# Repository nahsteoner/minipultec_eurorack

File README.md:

# OnerLAB BoCu

Module Eurorack **stéréo de fin de chaîne** : EQ type Pultec (sans tubes) + saturation douce à diodes + sorties jack 6,35 mm balanced.

- **Format** : 16 HP, 3U, alimentation ±12 V (header Doepfer 10 broches)
- **Entrées** : 2 × jack 3,5 mm mono (standard Eurorack), normalisées L → R
- **Sorties** : 2 × jack 6,35 mm TRS balanced (L / R)
- **PCB** : KiCad 7, netlist complète, **non routé** (placement fin + autorouter à ta main)
- **Fab** : pensé JLCPCB / LCSC, SMD 0603/0805 + SOIC-8

## Face avant

```
        OnerLAB BoCu
   [ LOW BOOST ]   [ LOW CUT ]
        [FREQ L] [FREQ R]     40 / 80 / 120 Hz
   [ MID CUT   ]   [ HIGH BOOST ]
   (LED sat L)         (LED sat R)
   IN L   IN R      OUT L   OUT R     ← jacks en bas
```

Les 4 pots sont **double piste** (L+R ensemble). Les deux rotatifs de fréquence sont **indépendants** (L et R).

## Le circuit, en une phrase

Buffer d'entrée → pad passif + mid-cut à gyrator → low-cut RC → makeup NE5532 avec **boost grave RLC (gyrator 11 H)** et **shelf aigu**, diodes Si/LED asymétriques dans la contre-réaction, puis driver balanced (hot + inverseur).

C'est un Pultec « inventé » en solide :

| Contrôle | Comportement simulé |
|---|---|
| Low boost | cloche ~+10 dB à 40 / 80 / 120 Hz, Q ≈ 1 |
| Low cut | shelf grave ~−11 dB, coin un peu au-dessus de f₀ |
| **Les deux** | le **Pultec trick** : bosse sur f₀ + creux de mud juste au-dessus |
| Mid cut | cloche ~−9 dB vers 500 Hz |
| High boost | shelf +8 à +10 dB vers 8–16 kHz |
| Diodes | propre à bas niveau (THD 0,08 % @ 0,5 V), couleur paire type lampe dès ~1,5 V |

Courbes : [`docs/curves/`](docs/curves/)

Relancer les sims : `python3 sim/simulate_bocu.py`

## Fichiers KiCad

| Fichier | Rôle |
|---|---|
| `hardware/OnerLAB_BoCu.kicad_pcb` | PCB 78 × 118 mm, 120 footprints, **94 nets**, ratsnest prêt |
| `hardware/OnerLAB_BoCu.net` | Netlist KiCad (source de vérité électrique) |
| `hardware/OnerLAB_BoCu_panel.kicad_pcb` | Face avant 16 HP, trous uniquement |
| `hardware/BOM_LCSC.csv` | BOM + codes LCSC (SMT) |
| `hardware/libraries/` | Switch 2P3T custom |

Pas de schéma dessiné : tout part de `tools/generate_kicad.py` (SKiDL). Tu n'en as pas besoin pour router.

### Chez toi dans KiCad 7

1. Ouvre `hardware/OnerLAB_BoCu.kicad_pcb`.
2. **Place** les SMD (ils sont en grille volontairement, les jacks/pots/switchs sont déjà en zone façade).
3. Ajoute un plan de masse GND (F.Cu et/ou B.Cu).
4. Autoroute : *Route → Automatically Route Selected* / FreeRouting, ou route à la main les alimentations d'abord.
5. DRC, puis Gerber JLCPCB (2 couches, 1,6 mm, HASL ou ENIG).

Régénérer netlist + PCB vierge :

```bash
python3 tools/generate_kicad.py
python3 tools/place_pcb.py
python3 tools/make_panel.py
```

## JLCPCB / LCSC

- **SMT assemblé** : NE5532DR (`C7426`, Basic), passifs 0603/0805, BAT54S, 1N4148W SOD-123, SS14, ferrites 0805.
- **THT à souder toi-même** (pas Basic JLCPCB) :
  - 2 × Thonkiconn **PJ398SM** (entrées 3,5)
  - 2 × **Neutrik NJ3FD-V** (sorties 6,35 TRS verticales) — un jack LCSC 6,35 vertical TRS peut remplacer, **adapte le footprint**
  - 4 × Alpha **RD902** B50K dual 9 mm
  - 2 × rotatif **SR16 2P3T 16 mm** — le footprint `OnerLAB:SW_Rotary_2P3T_SR16` est un **2×4 au pas 2,54 mm** (A1 A2 A3 A / B1 B2 B3 B). **Vérifie le pinout de TON switch** avant de router, ou déplace les pads.
  - header shrouded 2×5, stripe **rouge = pin 1 = −12 V**
  - 3 × LED 3 mm (pwr + sat L/R)

Les condensateurs qui fixent 40/80/120 Hz et le gyrator 10 nF sont en 0805. Pour un son plus « studio », tu peux remplacer les C de fréquence (1 µF+470 nF, 390 nF, 150 nF, 82/39/27 nF) par du **film THT 5 mm** — laisse des pastilles si tu veux.

Codes LCSC : **revérifie le stock / Basic vs Extended** sur [jlcpcb.com/parts](https://jlcpcb.com/parts) avant commande, les C-numbers bougent.

## Alim & niveaux

- ±12 V, ~80–100 mA / rail (5 × NE5532).
- Entrée ~10 Vpp Eurorack, Z = 100 kΩ, protection BAT54S.
- Sortie balanced un peu chaude (niveau Eurorack différentiel). Un interface ligne l'accepte en général ; sinon pad dans la DAW / l'entrée.

## Mapping pots (rheostat)

| Pot | CCW | CW |
|---|---|---|
| LOW BOOST, MID, HIGH | effet min (50 k) | max (≈ 0 Ω) |
| LOW CUT | bypass (0 Ω) | max cut (50 k) |

Pistes : 1-2-3 = canal L, 4-5-6 = canal R (Alpha RD902).

## Licence / nom

OnerLAB BoCu — projet DIY personnel. Pas un clone Pultec : topologie SSD (gyrators + diodes) calquée sur le *trick* boost+cut.

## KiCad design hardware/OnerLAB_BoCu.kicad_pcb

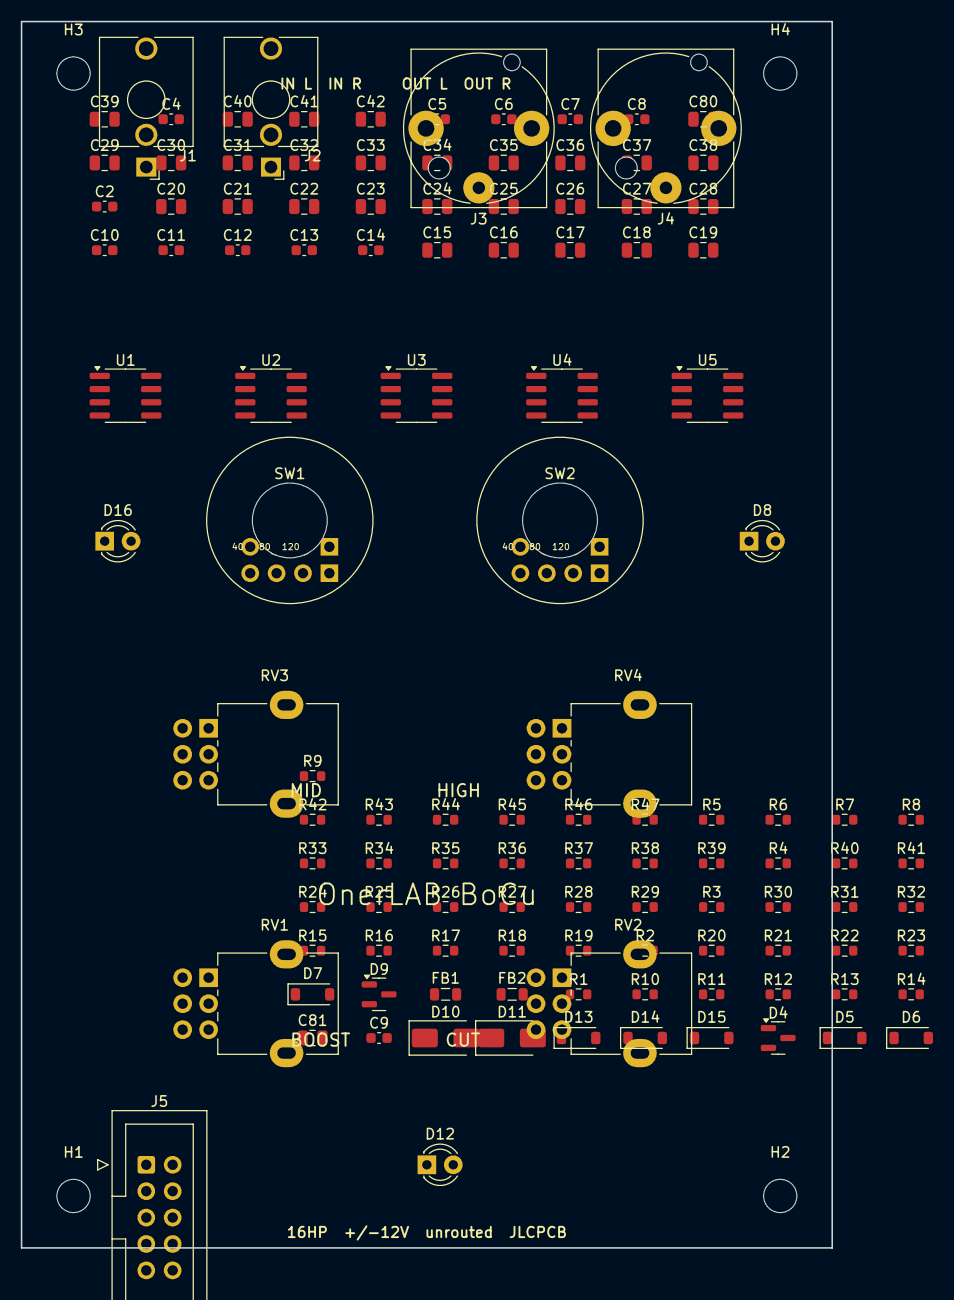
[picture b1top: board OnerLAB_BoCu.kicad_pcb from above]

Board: 2 copper layers, 78.0 x 118.0 mm, 124 parts (0 on the bottom side), 82 nets, no tracks yet.

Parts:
C2, C4, C5, C6, C7, C8, C9, C10, C11, C12, C13, C14: 100n; C_0603_1608Metric
C15, C27, C28, C29, C41, C42, C80, C81: 10u; C_0805_2012Metric
C16, C30: 100n; C_0805_2012Metric
C17, C26, C31, C40: 10n; C_0805_2012Metric
C18, C32: 82n; C_0805_2012Metric
C19, C33: 39n; C_0805_2012Metric
C20, C34: 27n; C_0805_2012Metric
C21, C35: 8.2n; C_0805_2012Metric
C22, C36: 1u; C_0805_2012Metric
C23, C37: 470n; C_0805_2012Metric
C24, C38: 390n; C_0805_2012Metric
C25, C39: 150n; C_0805_2012Metric
D4, D9: BAT54S; SOT-23
D5, D6, D7, D13, D14, D15: 1N4148W; D_SOD-123
D8, D16: LED_SAT; LED_D3.0mm
D10, D11: SS14; D_SMA
D12: LED_PWR; LED_D3.0mm
FB1, FB2: 600R@100MHz; L_0805_2012Metric
H1, H2, H3, H4: M3; MountingHole_3.2mm_M3
J1: IN_L_3.5; Jack_3.5mm_QingPu_WQP-PJ398SM_Vertical_CircularHoles
J2: IN_R_3.5; Jack_3.5mm_QingPu_WQP-PJ398SM_Vertical_CircularHoles
J3: OUT_L_6.35; Jack_6.35mm_Neutrik_NJ3FD-V_Vertical
J4: OUT_R_6.35; Jack_6.35mm_Neutrik_NJ3FD-V_Vertical
J5: EURORACK_10P; IDC-Header_2x05_P2.54mm_Vertical
R1, R7, R8, R9, R12, R19, R20, R30, R31, R32, R35, R42, R43: 10k; R_0603_1608Metric
R2, R22, R24, R25, R45, R47: 100k; R_0603_1608Metric
R3, R6, R26, R29: 1k; R_0603_1608Metric
R4, R5, R27, R28: 4.7k; R_0603_1608Metric
R10, R33: 15k; R_0603_1608Metric
R11, R15, R34, R38: 2.2k; R_0603_1608Metric
R13, R14, R36, R37: 22k; R_0603_1608Metric
R16, R39: 2.7k; R_0603_1608Metric
R17, R18, R40, R41: 33k; R_0603_1608Metric
R21, R23, R44, R46: 220R; R_0603_1608Metric
RV1: B50K_BOOST; Potentiometer_Alpha_RD902F-40-00D_Dual_Vertical
RV2: B50K_CUT; Potentiometer_Alpha_RD902F-40-00D_Dual_Vertical
RV3: B50K_MID; Potentiometer_Alpha_RD902F-40-00D_Dual_Vertical
RV4: B50K_HIGH; Potentiometer_Alpha_RD902F-40-00D_Dual_Vertical
SW1: FREQ_L; SW_Rotary_2P3T_SR16
SW2: FREQ_R; SW_Rotary_2P3T_SR16
U1, U2, U3, U4, U5: NE5532DR; SOIC-8_3.9x4.9mm_P1.27mm

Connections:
+12V: C2.1, C5.1, C7.1, C9.1, C11.1, C13.1, C80.1, D4.2, D9.2, FB1.2, R1.1, U1.8, U2.8, U3.8, U4.8, U5.8
-12V: C4.1, C6.1, C8.1, C10.1, C12.1, C14.1, C81.1, D4.1, D9.1, FB2.2, U1.4, U2.4, U3.4, U4.4, U5.4
GND: C2.2, C4.2, C5.2, C6.2, C7.2, C8.2, C9.2, C10.2, C11.2, C12.2, C13.2, C14.2, C17.2, C21.2, C26.2, C31.2, C35.2, C40.2, C80.2, C81.2, D12.1, J1.S, J2.S, J3.S, J4.S, J5.2, J5.3, J5.4, J5.5, J5.6, R2.2, R5.2, R9.2, R12.2, R22.2, R24.2, R25.2, R28.2, R32.2, R35.2, R45.2, R47.2, U2.5, U4.5
IN_L: C15.1, J1.T, J2.TN, R2.1
IN_R: C29.1, J2.T, R25.1
L_BLK: D4.3, R3.2, U1.3
L_BUF: R4.1, U1.1, U1.2
L_COLD: R20.2, R23.1, U2.7
L_D3: D7.1, R13.1
L_EQ: R4.2, R5.1, R6.1, RV2.1, SW1.B
L_HI: R15.2, RV4.2
L_INVN: R19.2, R20.1, U2.6
L_LB: R16.2, RV1.2
L_LC: RV1.3, SW1.A
L_LG+: C26.1, R17.2, U1.5
L_LL: C22.2, C23.2, C24.2, C25.2, R17.1, R18.2
L_MIDC: C16.1, RV3.3
L_MIDG+: C17.1, R7.2, U5.3
L_MIDL: C16.2, R7.1, R8.2
L_MIDW: R6.2, RV3.2
L_MK: D5.2, R10.1, R14.2, R19.1, R21.1, U2.1
L_NINV: D8.2, R10.2, R11.1, R13.2, R15.1, R16.1, U2.2
L_POST: C18.2, C19.2, C20.2, R9.1, RV2.2, U2.3
L_TAP: R11.2, R12.1
unnamed: D10.1, FB1.1
unnamed: D11.2, FB2.1
unnamed: D12.2, R1.2
unnamed: C15.2, R3.1
unnamed: R8.1, U5.1, U5.2
unnamed: C18.1, SW1.B1
unnamed: C19.1, SW1.B2
unnamed: C20.1, SW1.B3
unnamed: D5.1, D6.2
unnamed: D6.1, D7.2
unnamed: D8.1, R14.1
unnamed: C21.1, RV4.3
unnamed: C22.1, C23.1, SW1.A1
unnamed: C24.1, SW1.A2
unnamed: C25.1, SW1.A3
unnamed: R18.1, U1.6, U1.7
unnamed: C27.2, J3.T, R22.1
unnamed: C27.1, R21.2
unnamed: C28.2, J3.R, R24.1
unnamed: C28.1, R23.2
unnamed: C29.2, R26.1
unnamed: R31.1, U5.6, U5.7
unnamed: C32.1, SW2.B1
unnamed: C33.1, SW2.B2
unnamed: C34.1, SW2.B3
unnamed: D13.1, D14.2
unnamed: D14.1, D15.2
unnamed: D16.1, R37.1
unnamed: C35.1, RV4.6
unnamed: C36.1, C37.1, SW2.A1
unnamed: C38.1, SW2.A2
unnamed: C39.1, SW2.A3
unnamed: R41.1, U3.6, U3.7
unnamed: C41.2, J4.T, R45.1
unnamed: C41.1, R44.2
unnamed: C42.2, J4.R, R47.1
unnamed: C42.1, R46.2
RAW+12: D10.2, J5.7, J5.8
RAW-12: D11.1, J5.1
R_BLK: D9.3, R26.2, U3.3
R_BUF: R27.1, U3.1, U3.2
R_COLD: R43.2, R46.1, U4.7
R_D3: D15.1, R36.1
R_EQ: R27.2, R28.1, R29.1, RV2.4, SW2.B
R_HI: R38.2, RV4.5
R_INVN: R42.2, R43.1, U4.6
R_LB: R39.2, RV1.5
R_LC: RV1.6, SW2.A
R_LG+: C40.1, R40.2, U3.5
R_LL: C36.2, C37.2, C38.2, C39.2, R40.1, R41.2
R_MIDC: C30.1, RV3.6
R_MIDG+: C31.1, R30.2, U5.5
R_MIDL: C30.2, R30.1, R31.2
R_MIDW: R29.2, RV3.5
R_MK: D13.2, R33.1, R37.2, R42.1, R44.1, U4.1
R_NINV: D16.2, R33.2, R34.1, R36.2, R38.1, R39.1, U4.2
R_POST: C32.2, C33.2, C34.2, R32.1, RV2.5, U4.3
R_TAP: R34.2, R35.1

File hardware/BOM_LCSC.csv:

Reference,Value,Footprint,LCSC,Mount,Notes
C10,100n,Capacitor_SMD:C_0603_1608Metric,C14663,SMT,
C11,100n,Capacitor_SMD:C_0603_1608Metric,C14663,SMT,
C12,100n,Capacitor_SMD:C_0603_1608Metric,C14663,SMT,
C13,100n,Capacitor_SMD:C_0603_1608Metric,C14663,SMT,
C14,100n,Capacitor_SMD:C_0603_1608Metric,C14663,SMT,
C15,10u,Capacitor_SMD:C_0805_2012Metric,C15850,SMT,
C16,100n,Capacitor_SMD:C_0805_2012Metric,C49678,SMT,
C17,10n,Capacitor_SMD:C_0805_2012Metric,C1710,SMT,
C18,82n,Capacitor_SMD:C_0805_2012Metric,C39616,SMT,
C19,39n,Capacitor_SMD:C_0805_2012Metric,C1653,SMT,
C2,100n,Capacitor_SMD:C_0603_1608Metric,C14663,SMT,
C20,27n,Capacitor_SMD:C_0805_2012Metric,C1548,SMT,
C21,8.2n,Capacitor_SMD:C_0805_2012Metric,C1804,SMT,
C22,1u,Capacitor_SMD:C_0805_2012Metric,C28323,SMT,
C23,470n,Capacitor_SMD:C_0805_2012Metric,C1713,SMT,
C24,390n,Capacitor_SMD:C_0805_2012Metric,C1328,SMT,
C25,150n,Capacitor_SMD:C_0805_2012Metric,C66719,SMT,
C26,10n,Capacitor_SMD:C_0805_2012Metric,C1710,SMT,
C27,10u,Capacitor_SMD:C_0805_2012Metric,C15850,SMT,
C28,10u,Capacitor_SMD:C_0805_2012Metric,C15850,SMT,
C29,10u,Capacitor_SMD:C_0805_2012Metric,C15850,SMT,
C30,100n,Capacitor_SMD:C_0805_2012Metric,C49678,SMT,
C31,10n,Capacitor_SMD:C_0805_2012Metric,C1710,SMT,
C32,82n,Capacitor_SMD:C_0805_2012Metric,C39616,SMT,
C33,39n,Capacitor_SMD:C_0805_2012Metric,C1653,SMT,
C34,27n,Capacitor_SMD:C_0805_2012Metric,C1548,SMT,
C35,8.2n,Capacitor_SMD:C_0805_2012Metric,C1804,SMT,
C36,1u,Capacitor_SMD:C_0805_2012Metric,C28323,SMT,
C37,470n,Capacitor_SMD:C_0805_2012Metric,C1713,SMT,
C38,390n,Capacitor_SMD:C_0805_2012Metric,C1328,SMT,
C39,150n,Capacitor_SMD:C_0805_2012Metric,C66719,SMT,
C4,100n,Capacitor_SMD:C_0603_1608Metric,C14663,SMT,
C40,10n,Capacitor_SMD:C_0805_2012Metric,C1710,SMT,
C41,10u,Capacitor_SMD:C_0805_2012Metric,C15850,SMT,
C42,10u,Capacitor_SMD:C_0805_2012Metric,C15850,SMT,
C5,100n,Capacitor_SMD:C_0603_1608Metric,C14663,SMT,
C6,100n,Capacitor_SMD:C_0603_1608Metric,C14663,SMT,
C7,100n,Capacitor_SMD:C_0603_1608Metric,C14663,SMT,
C8,100n,Capacitor_SMD:C_0603_1608Metric,C14663,SMT,
C80,10u,Capacitor_SMD:C_0805_2012Metric,C15850,SMT,
C81,10u,Capacitor_SMD:C_0805_2012Metric,C15850,SMT,
C9,100n,Capacitor_SMD:C_0603_1608Metric,C14663,SMT,
D10,SS14,Diode_SMD:D_SMA,C8678,SMT,
D11,SS14,Diode_SMD:D_SMA,C8678,SMT,
D12,LED_PWR,LED_THT:LED_D3.0mm,C72038,THT,
D13,1N4148W,Diode_SMD:D_SOD-123,C2128,SMT,
D14,1N4148W,Diode_SMD:D_SOD-123,C2128,SMT,
D15,1N4148W,Diode_SMD:D_SOD-123,C2128,SMT,
D16,LED_SAT,LED_THT:LED_D3.0mm,C72038,THT,
D4,BAT54S,Package_TO_SOT_SMD:SOT-23,C8547,SMT,
D5,1N4148W,Diode_SMD:D_SOD-123,C2128,SMT,
D6,1N4148W,Diode_SMD:D_SOD-123,C2128,SMT,
D7,1N4148W,Diode_SMD:D_SOD-123,C2128,SMT,
D8,LED_SAT,LED_THT:LED_D3.0mm,C72038,THT,
D9,BAT54S,Package_TO_SOT_SMD:SOT-23,C8547,SMT,
FB1,600R@100MHz,Inductor_SMD:L_0805_2012Metric,C16762,SMT,
FB2,600R@100MHz,Inductor_SMD:L_0805_2012Metric,C16762,SMT,
J1,IN_L_3.5,Connector_Audio:Jack_3.5mm_QingPu_WQP-PJ398SM_Vertical_CircularHoles,,THTThonk PJ398SM / WQP-PJ398SM (pas JLCPCB)
J2,IN_R_3.5,Connector_Audio:Jack_3.5mm_QingPu_WQP-PJ398SM_Vertical_CircularHoles,,THTThonk PJ398SM / WQP-PJ398SM (pas JLCPCB)
J3,OUT_L_6.35,Connector_Audio:Jack_6.35mm_Neutrik_NJ3FD-V_Vertical,,THTNeutrik NJ3FD-V — alt. LCSC jack 6.35 TRS vertical
J4,OUT_R_6.35,Connector_Audio:Jack_6.35mm_Neutrik_NJ3FD-V_Vertical,,THTNeutrik NJ3FD-V — alt. LCSC jack 6.35 TRS vertical
J5,EURORACK_10P,Connector_IDC:IDC-Header_2x05_P2.54mm_Vertical,,THTHeader shrouded 2x5 2.54mm, stripe rouge = pin1 = -12V
R1,10k,Resistor_SMD:R_0603_1608Metric,C25803,SMT,
R10,15k,Resistor_SMD:R_0603_1608Metric,C22847,SMT,
R11,2.2k,Resistor_SMD:R_0603_1608Metric,C17630,SMT,
R12,10k,Resistor_SMD:R_0603_1608Metric,C25803,SMT,
R13,22k,Resistor_SMD:R_0603_1608Metric,C14611,SMT,
R14,22k,Resistor_SMD:R_0603_1608Metric,C14611,SMT,
R15,2.2k,Resistor_SMD:R_0603_1608Metric,C17630,SMT,
R16,2.7k,Resistor_SMD:R_0603_1608Metric,C22933,SMT,
R17,33k,Resistor_SMD:R_0603_1608Metric,C23214,SMT,
R18,33k,Resistor_SMD:R_0603_1608Metric,C23214,SMT,
R19,10k,Resistor_SMD:R_0603_1608Metric,C25803,SMT,
R2,100k,Resistor_SMD:R_0603_1608Metric,C1790,SMT,
R20,10k,Resistor_SMD:R_0603_1608Metric,C25803,SMT,
R21,220R,Resistor_SMD:R_0603_1608Metric,C14754,SMT,
R22,100k,Resistor_SMD:R_0603_1608Metric,C1790,SMT,
R23,220R,Resistor_SMD:R_0603_1608Metric,C14754,SMT,
R24,100k,Resistor_SMD:R_0603_1608Metric,C1790,SMT,
R25,100k,Resistor_SMD:R_0603_1608Metric,C1790,SMT,
R26,1k,Resistor_SMD:R_0603_1608Metric,C11702,SMT,
R27,4.7k,Resistor_SMD:R_0603_1608Metric,C13305,SMT,
R28,4.7k,Resistor_SMD:R_0603_1608Metric,C13305,SMT,
R29,1k,Resistor_SMD:R_0603_1608Metric,C11702,SMT,
R3,1k,Resistor_SMD:R_0603_1608Metric,C11702,SMT,
R30,10k,Resistor_SMD:R_0603_1608Metric,C25803,SMT,
R31,10k,Resistor_SMD:R_0603_1608Metric,C25803,SMT,
R32,10k,Resistor_SMD:R_0603_1608Metric,C25803,SMT,
R33,15k,Resistor_SMD:R_0603_1608Metric,C22847,SMT,
R34,2.2k,Resistor_SMD:R_0603_1608Metric,C17630,SMT,
R35,10k,Resistor_SMD:R_0603_1608Metric,C25803,SMT,
R36,22k,Resistor_SMD:R_0603_1608Metric,C14611,SMT,
R37,22k,Resistor_SMD:R_0603_1608Metric,C14611,SMT,
R38,2.2k,Resistor_SMD:R_0603_1608Metric,C17630,SMT,
R39,2.7k,Resistor_SMD:R_0603_1608Metric,C22933,SMT,
R4,4.7k,Resistor_SMD:R_0603_1608Metric,C13305,SMT,
R40,33k,Resistor_SMD:R_0603_1608Metric,C23214,SMT,
R41,33k,Resistor_SMD:R_0603_1608Metric,C23214,SMT,
R42,10k,Resistor_SMD:R_0603_1608Metric,C25803,SMT,
R43,10k,Resistor_SMD:R_0603_1608Metric,C25803,SMT,
R44,220R,Resistor_SMD:R_0603_1608Metric,C14754,SMT,
R45,100k,Resistor_SMD:R_0603_1608Metric,C1790,SMT,
R46,220R,Resistor_SMD:R_0603_1608Metric,C14754,SMT,
R47,100k,Resistor_SMD:R_0603_1608Metric,C1790,SMT,
R5,4.7k,Resistor_SMD:R_0603_1608Metric,C13305,SMT,
R6,1k,Resistor_SMD:R_0603_1608Metric,C11702,SMT,
R7,10k,Resistor_SMD:R_0603_1608Metric,C25803,SMT,
R8,10k,Resistor_SMD:R_0603_1608Metric,C25803,SMT,
R9,10k,Resistor_SMD:R_0603_1608Metric,C25803,SMT,
RV1,B50K_BOOST,Potentiometer_THT:Potentiometer_Alpha_RD902F-40-00D_Dual_Vertical,,THTAlpha RD902F B50K dual 9mm (Thonk / modular)
RV2,B50K_CUT,Potentiometer_THT:Potentiometer_Alpha_RD902F-40-00D_Dual_Vertical,,THTAlpha RD902F B50K dual 9mm
RV3,B50K_MID,Potentiometer_THT:Potentiometer_Alpha_RD902F-40-00D_Dual_Vertical,,THTAlpha RD902F B50K dual 9mm
RV4,B50K_HIGH,Potentiometer_THT:Potentiometer_Alpha_RD902F-40-00D_Dual_Vertical,,THTAlpha RD902F B50K dual 9mm
SW1,FREQ_L,OnerLAB:SW_Rotary_2P3T_SR16,,THTSR16 2P3T 16mm — VERIFIER le pinout vs footprint OnerLAB
SW2,FREQ_R,OnerLAB:SW_Rotary_2P3T_SR16,,THTSR16 2P3T 16mm — VERIFIER le pinout vs footprint OnerLAB
U1,NE5532DR,Package_SO:SOIC-8_3.9x4.9mm_P1.27mm,C7426,SMT,
U2,NE5532DR,Package_SO:SOIC-8_3.9x4.9mm_P1.27mm,C7426,SMT,
U3,NE5532DR,Package_SO:SOIC-8_3.9x4.9mm_P1.27mm,C7426,SMT,
U4,NE5532DR,Package_SO:SOIC-8_3.9x4.9mm_P1.27mm,C7426,SMT,
U5,NE5532DR,Package_SO:SOIC-8_3.9x4.9mm_P1.27mm,C7426,SMT,
